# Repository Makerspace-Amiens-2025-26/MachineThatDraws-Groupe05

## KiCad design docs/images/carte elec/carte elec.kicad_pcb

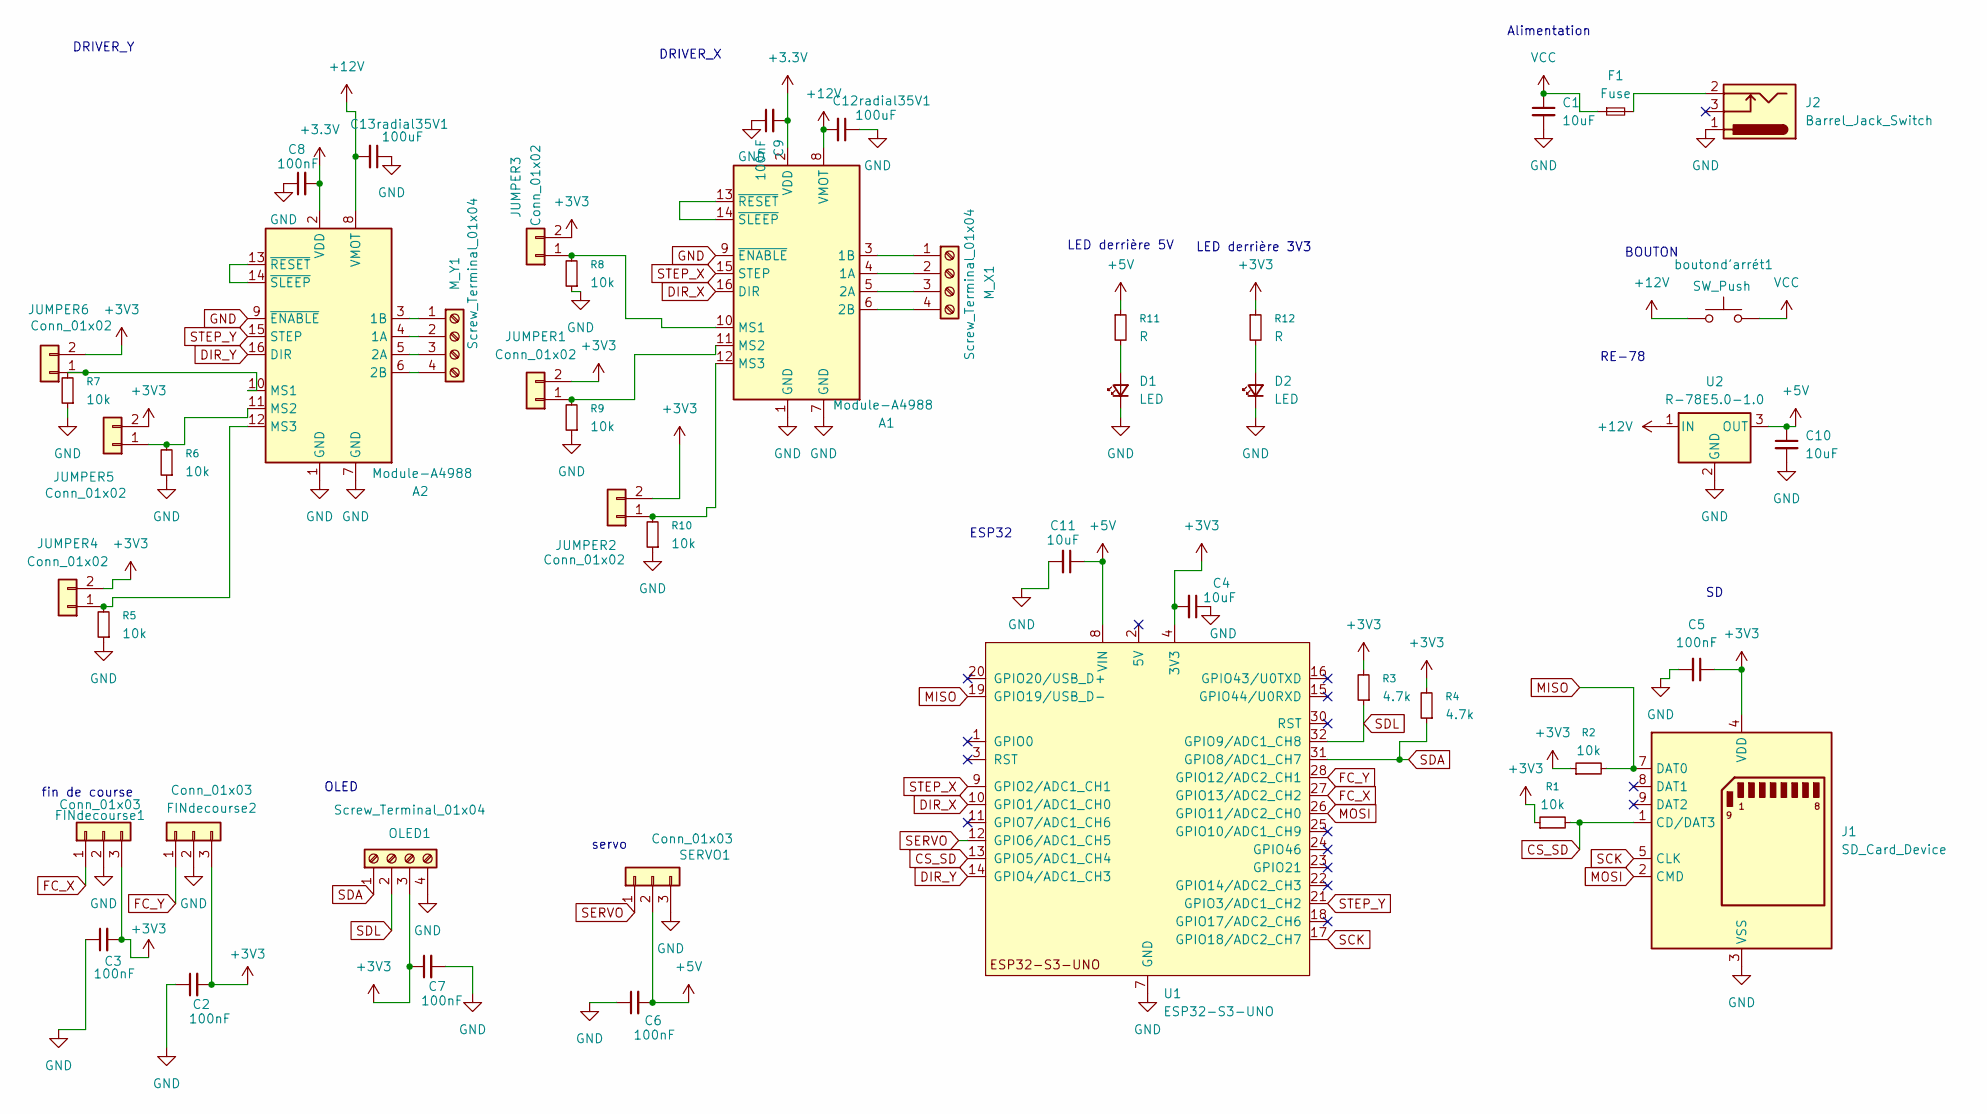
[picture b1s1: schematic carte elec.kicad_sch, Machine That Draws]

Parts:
A1, A2: Module-A4988; Pololu_Breakout-16_15.2x20.3mm
C1, C4, C10, C11: 10uF; C_1206
C2, C3, C5, C6, C7, C8, C9: 100nF; C_1206
C12radial35V1, C13radial35V1: 100uF; C_Radial_D6.3mm_H11.0mm_P2.50mm
D1, D2: LED; LED_0805_2012Metric
F1: Fuse; Fuse_1206_3216Metric
FINdecourse1, FINdecourse2: Conn_01x03; PinSocket_1x03_P2.54mm_Vertical
J1: SD_Card_Device; SD_Hirose_DM1AA_SF_PEJ82
J2: Barrel_Jack_Switch; BarrelJack_CUI_PJ-036AH-SMT_Horizontal
JUMPER1, JUMPER2, JUMPER3, JUMPER4, JUMPER5, JUMPER6: Conn_01x02; PinHeader_1x02_P2.54mm_Vertical
M_X1: Screw_Terminal_01x04; PinHeader_1x04_P2.54mm_Vertical
M_Y1: Screw_Terminal_01x04; PinHeader_1x04_P2.54mm_Vertical
OLED1: Screw_Terminal_01x04; PinHeader_1x04_P2.54mm_Vertical
R1, R2, R5, R6, R7, R8, R9, R10: 10k; R_1206
R3, R4: 4.7k; R_1206
R11, R12: R; R_1206
SERVO1: Conn_01x03; PinHeader_1x03_P2.54mm_Vertical
U1: ESP32-S3-UNO; ESP_S3_UNO
U2: R-78E5.0-1.0; Converter_DCDC_RECOM_R-78E-0.5_THT
boutond'arrét1: SW_Push; SW_Push_KMR2

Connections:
+3.3V: A1.2 (VDD), A2.2 (VDD), C8.2, C9.2
+3V3: C2.2, C3.2, C4.2, C5.1, C7.1, FINdecourse1.3, FINdecourse2.3, J1.4 (VDD), JUMPER1.2, JUMPER2.2, JUMPER3.2, JUMPER4.2, JUMPER5.2, JUMPER6.2, OLED1.3, R1.1, R2.1, R3.2, R4.2, R12.1, U1.4 (3V3)
+5V: C6.2, C10.1, C11.1, R11.1, SERVO1.2, U1.8 (VIN), U2.3 (OUT)
+12V: A1.8 (VMOT), A2.8 (VMOT), C12radial35V1.2, C13radial35V1.2, U2.1 (IN), boutond'arrét1.1
CS_SD: J1.1 (CD/DAT3), R1.2, U1.13 (GPIO5/ADC1_CH4)
DIR_X: A1.16 (DIR), U1.10 (GPIO1/ADC1_CH0)
DIR_Y: A2.16 (DIR), U1.14 (GPIO4/ADC1_CH3)
FC_X: FINdecourse1.1, U1.27 (GPIO13/ADC2_CH2)
FC_Y: FINdecourse2.1, U1.28 (GPIO12/ADC2_CH1)
GND: A1.1 (GND), A1.7 (GND), A1.9 (~ENABLE), A2.1 (GND), A2.7 (GND), A2.9 (~ENABLE), C1.2, C2.1, C3.1, C4.1, C5.2, C6.1, C7.2, C8.1, C9.1, C10.2, C11.2, C12radial35V1.1, C13radial35V1.1, D1.1 (K), D2.1 (K), FINdecourse1.2, FINdecourse2.2, J1.3 (VSS), J1.6 (VSS), J2.1, OLED1.4, R5.1, R6.1, R7.1, R8.1, R9.1, R10.1, SERVO1.3, U1.6 (GND), U1.7 (GND), U1.29 (GND), U2.2 (GND)
MISO: J1.7 (DAT0), R2.2, U1.19 (GPIO19/USB_D-)
MOSI: J1.2 (CMD), U1.26 (GPIO11/ADC2_CH0)
unnamed: A1.4 (1A), M_X1.2
unnamed: A1.3 (1B), M_X1.1
unnamed: A1.5 (2A), M_X1.3
unnamed: A1.6 (2B), M_X1.4
unnamed: A1.10 (MS1), JUMPER3.1, R8.2
unnamed: A1.11 (MS2), JUMPER1.1, R9.2
unnamed: A1.12 (MS3), JUMPER2.1, R10.2
unnamed: A1.13 (~RESET), A1.14 (~SLEEP)
unnamed: A2.4 (1A), M_Y1.2
unnamed: A2.3 (1B), M_Y1.1
unnamed: A2.5 (2A), M_Y1.3
unnamed: A2.6 (2B), M_Y1.4
unnamed: A2.10 (MS1), JUMPER6.1, R7.2
unnamed: A2.11 (MS2), JUMPER5.1, R6.2
unnamed: A2.12 (MS3), JUMPER4.1, R5.2
unnamed: A2.13 (~RESET), A2.14 (~SLEEP)
unnamed: D1.2 (A), R11.2
unnamed: D2.2 (A), R12.2
unnamed: F1.2, J2.2
SCK: J1.5 (CLK), U1.17 (GPIO18/ADC2_CH7)
SDA: OLED1.1, R4.1, U1.31 (GPIO8/ADC1_CH7)
SDL: OLED1.2, R3.1, U1.32 (GPIO9/ADC1_CH8)
SERVO: SERVO1.1, U1.12 (GPIO6/ADC1_CH5)
STEP_X: A1.15 (STEP), U1.9 (GPIO2/ADC1_CH1)
STEP_Y: A2.15 (STEP), U1.21 (GPIO3/ADC1_CH2)
VCC: C1.1, F1.1, boutond'arrét1.2

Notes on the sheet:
OLED
LED derrière 3V3
LED derrière 5V
fin de course
DRIVER_Y
Alimentation
ESP32
BOUTON
servo
RE-78
DRIVER_X

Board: 2 copper layers, 47 parts (0 on the bottom side), 38 nets, no tracks yet.

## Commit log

2026-01-30 video
2026-01-30 changement v
2026-01-30 fin video
2026-01-30 taille
2026-01-30 couleur sur le site
2026-01-30 changement
2026-01-30 couleur
2026-01-30 j espere ça marche
2026-04-24 Validation PCB pour production
2026-04-27 fix wiring problems
2026-06-03 ajouts fichiers
2026-06-03 index
2026-06-05 Create Doc final
2026-06-05 add sites
2026-06-05 update elec
2026-06-05 move CSS
2026-06-05 testing CI CD minimal
2026-06-05 Clean Github Actions
2026-06-05 Fix typo
2026-06-05 fix path to JS
2026-06-06 image
2026-06-06 meca
2026-06-06 espoir
2026-06-06 comme avant
2026-06-09 poster
